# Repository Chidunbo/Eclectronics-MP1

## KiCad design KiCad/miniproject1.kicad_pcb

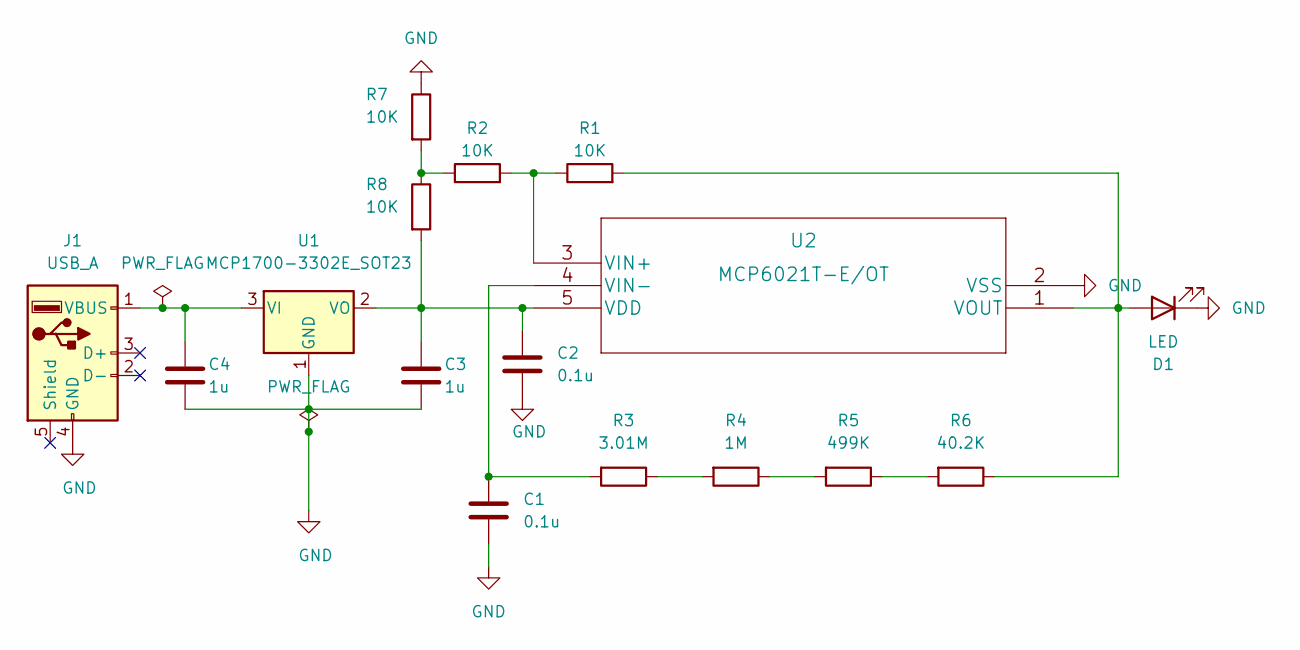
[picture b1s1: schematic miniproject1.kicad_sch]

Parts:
C1, C2: 0.1u; CAPC1608X90
C3, C4: 1u; C0603C105K3RACTU
D1: LED; D_0805_2012Metric
J1: USB_A; MOLEX_48037-0001 (2)
R1, R2, R7, R8: 10K; RC0603FR-0710KL
R3: 3.01M; R_0603_1608Metric
R4: 1M; RC0603FR-071ML
R5: 499K; RC0603FR-07499KL
R6: 40.2K; RC0603FR-0740K2L
U1: MCP1700-3302E_SOT23; MCP1702T-3302E&slash_CB
U2: MCP6021T-E/OT; MCP6021T-E&slash_OT

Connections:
GND: C1.2, C2.2, C3.2, C4.2, D1.1 (K), J1.4 (GND), R7.1, U1.1 (GND), U2.2 (VSS)
unnamed: C1.1, R3.2, U2.4 (VIN-)
unnamed: C2.1, C3.1, R8.2, U1.2 (VO), U2.5 (VDD)
unnamed: C4.1, J1.1 (VBUS), U1.3 (VI)
unnamed: D1.2 (A), R1.2, R6.1, U2.1 (VOUT)
unnamed: R1.1, R2.2, U2.3 (VIN+)
unnamed: R2.1, R7.2, R8.1
unnamed: R3.1, R4.2
unnamed: R4.1, R5.2
unnamed: R5.1, R6.2

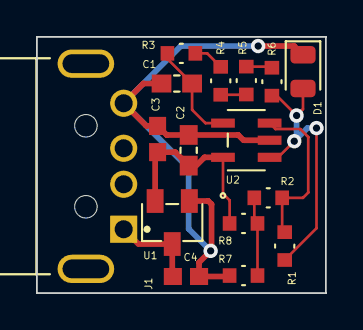
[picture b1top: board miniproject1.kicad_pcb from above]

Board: 2 copper layers, 16.1 x 14.2 mm, 16 parts (0 on the bottom side), 10 nets.

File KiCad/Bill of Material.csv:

"Source:","C:\Users\jLiu2\Desktop\Eclectronics\miniproject1\miniproject1.kicad_sch"
"Date:","9/16/2022 12:00:45 PM"
"Tool:","Eeschema (6.0.7)"
"Generator:","C:\Users\jLiu2\Downloads\6.0\bin\scripting\plugins/bom_csv_grouped_by_value_with_fp.py"
"Component Count:","16"
"Ref","Qnty","Value","Cmp name","Footprint","Description","Vendor"
"C1, C2, ","2","0.1u","C","miniproject1-library:CAPC1608X90","Unpolarized capacitor",""
"C3, C4, ","2","1u","C","miniproject1-library:C0603C105K3RACTU","Unpolarized capacitor",""
"D1, ","1","LED","LED","Diode_SMD:D_0805_2012Metric","Light emitting diode",""
"J1, ","1","USB_A","USB_A","miniproject1-library:MOLEX_48037-0001 (2)","USB Type A connector",""
"R1, R2, R7, R8, ","4","10K","R","miniproject1-library:RC0603FR-0710KL","Resistor",""
"R3, ","1","3.01M","R","Resistor_SMD:R_0603_1608Metric","Resistor",""
"R4, ","1","1M","R","miniproject1-library:RC0603FR-071ML","Resistor",""
"R5, ","1","499K","R","miniproject1-library:RC0603FR-07499KL","Resistor",""
"R6, ","1","40.2K","R","miniproject1-library:RC0603FR-0740K2L","Resistor",""
"U1, ","1","MCP1700-3302E_SOT23","MCP1700-3302E_SOT23","miniproject1-library:MCP1702T-3302E&slash_CB","250mA Low Quiscent Current LDO, 3.3V output, SOT-23",""
"U2, ","1","MCP6021T-E/OT","MCP6021T-E{slash}OT","miniproject1-library:MCP6021T-E&slash_OT","",""

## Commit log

2022-09-16 Add all files for MP1
2022-09-16 Add bill of material sheet

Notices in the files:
parts and their libraries:
Copyright 2021 Accelerated Designs. All rights reserved.
